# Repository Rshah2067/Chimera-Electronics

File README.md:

# Chimera-Electronics
Chimera is a beetleweight combat robot being designed to compete at NHRL. It has a flamethrower as a main weapon and 2 lifting forks to high center and burn the underside of opponents. This project has the Kicad designs for the custom PCB that controls the robot.

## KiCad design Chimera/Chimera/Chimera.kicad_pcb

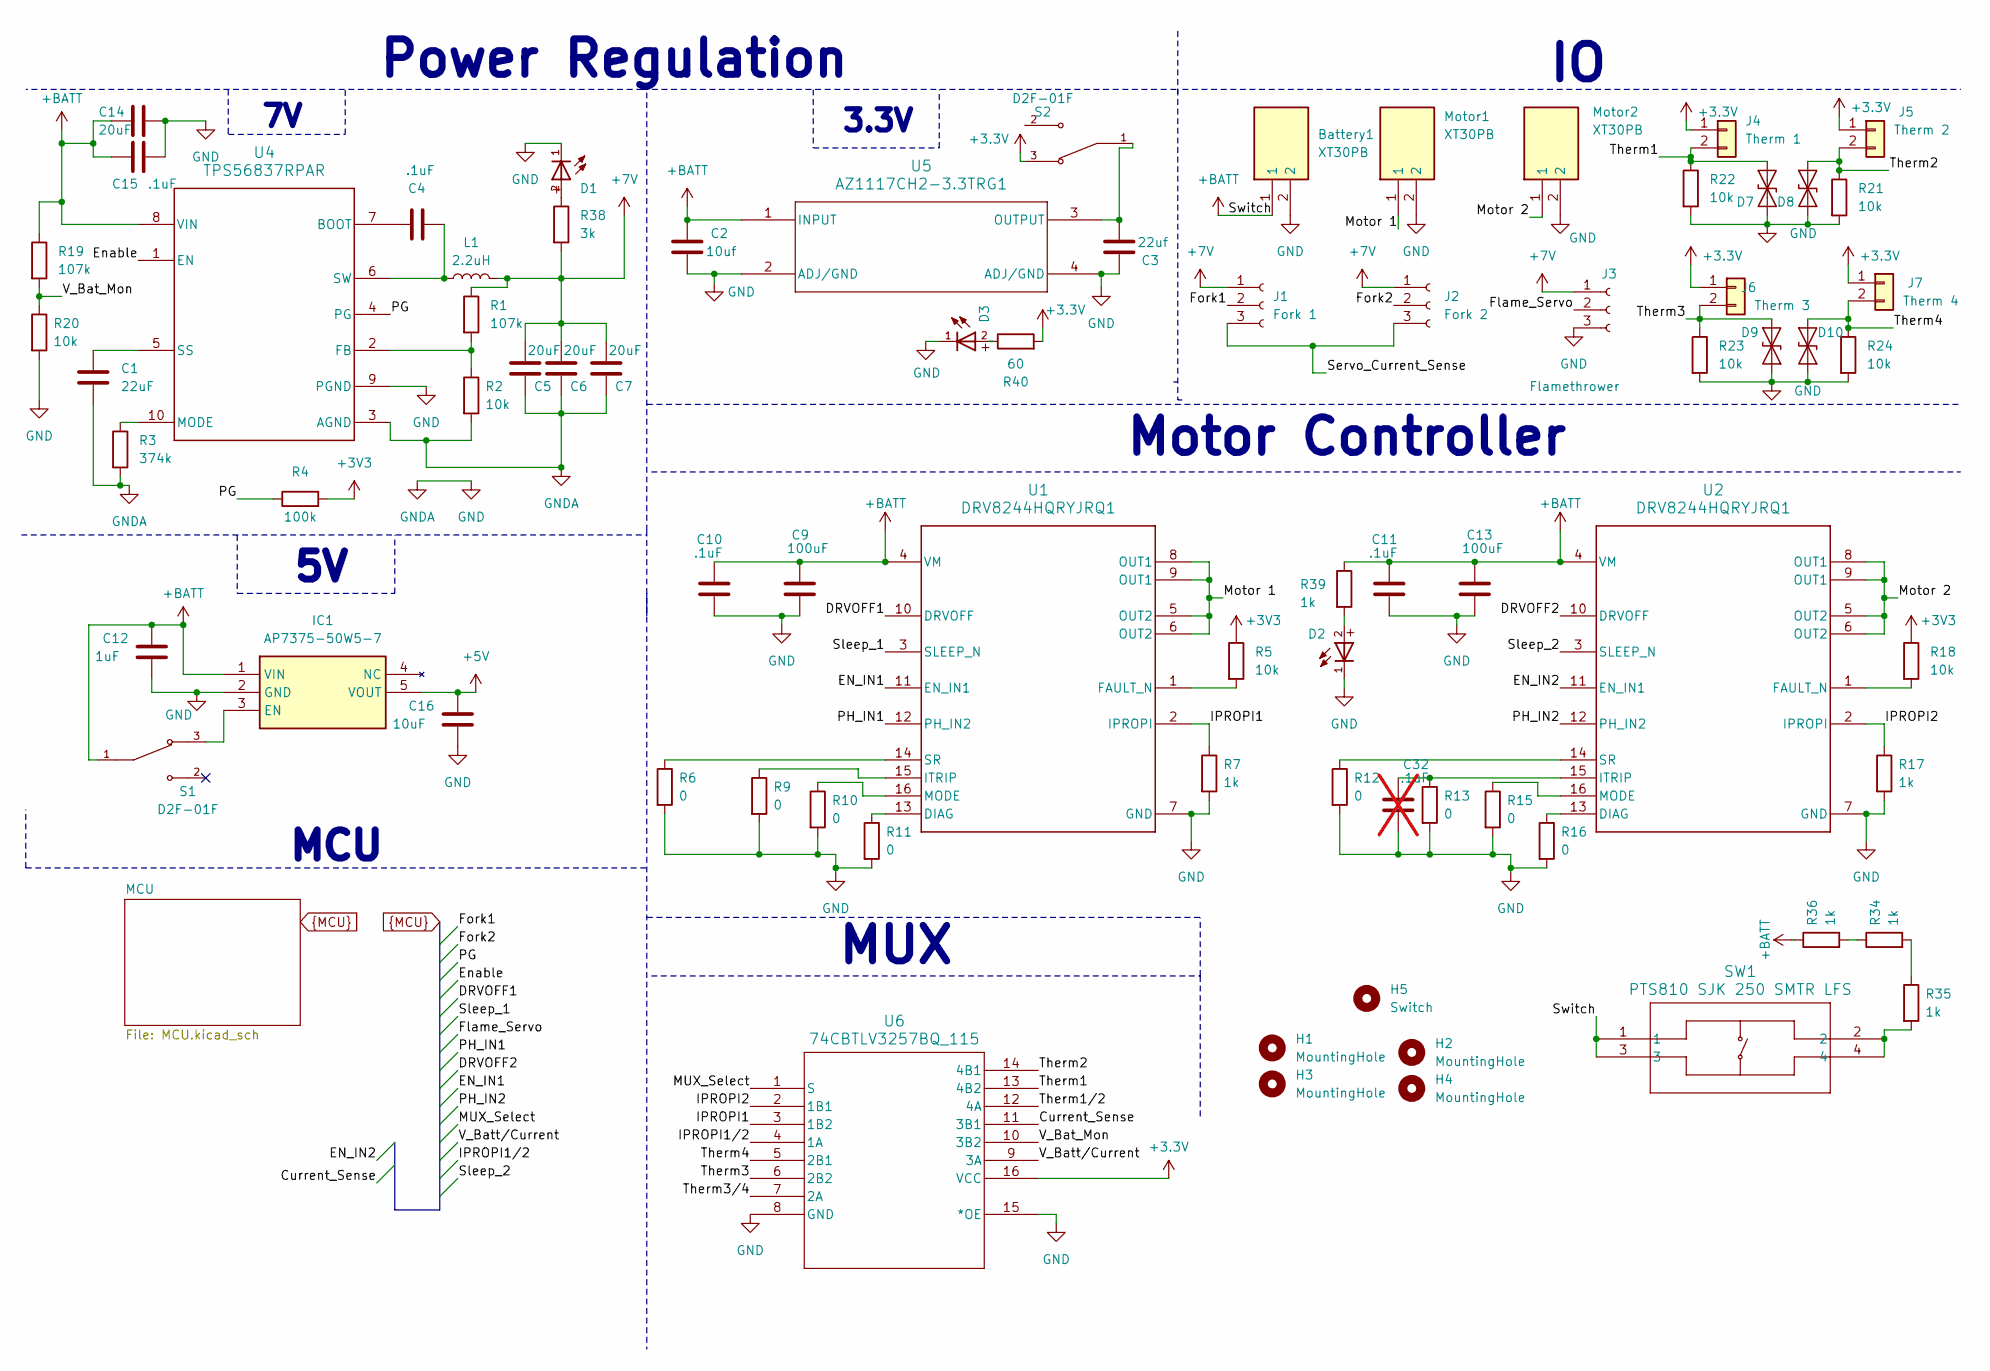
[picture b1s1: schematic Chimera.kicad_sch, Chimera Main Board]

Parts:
Battery1: XT30PB; Manufacturer_Part_Number XT30PB
C1: 22uF; C_0805_2012Metric
C2: 10uf; C_0805_2012Metric
C3: 22uf; C_0805_2012Metric
C4, C10, C11, C15: .1uF; C_0805_2012Metric
C5, C6, C7, C14: 20uF; CAPC1810X80N
C9, C13: 100uF; PCAP_6.3x7.7-ELECT_NCA-M
C12: 1uF; C_0805_2012Metric
C16: 10uF; C_0805_2012Metric
C32: .1uF; C_0805_2012Metric; not fitted
D1, D2, D3: WL-SMCD_0603
D7, D8, D9, D10: SMAJ8.0CA; D_0603_1608Metric
H1, H2, H3, H4: MountingHole; MountingHole_3.2mm_M3
H5: Switch; MountingHole_3.2mm_M3
IC1: AP7375-50W5-7; SOT95P285X140-5N; Manufacturer_Part_Number AP7375-50W5-7; Mouser Part Number 621-AP7375-50W5-7
J1: Fork 1; PinSocket_1x03_P2.54mm_Vertical
J2: Fork 2; PinSocket_1x03_P2.54mm_Vertical
J3: Flamethrower; PinSocket_1x03_P2.54mm_Vertical
J4: Therm 1; PinSocket_1x02_P2.54mm_Vertical
J5: Therm 2; PinSocket_1x02_P2.54mm_Vertical
J6: Therm 3; PinSocket_1x02_P2.54mm_Vertical
J7: Therm 4; PinSocket_1x02_P2.54mm_Vertical
L1: 2.2uH; IND_IHLP-3232DZ_VIS-L
Motor1, Motor2: XT30PB; Manufacturer_Part_Number XT30PB
R1, R19: 107k; R_0805_2012Metric
R2, R5, R18, R20, R21, R22, R23, R24: 10k; R_0805_2012Metric
R3: 374k; R_0805_2012Metric
R4: 100k; R_0805_2012Metric
R6, R9, R10, R11, R12, R13, R15, R16: 0; R_0805_2012Metric
R7, R17, R34, R35, R36, R39: 1k; R_0805_2012Metric
R38: 3k; R_0805_2012Metric
R40: 60; R_0805_2012Metric
S1, S2: D2F-01F; SW_D2F-01F; PARTREV B036-E1-12
SW1: PTS810 SJK 250 SMTR LFS; PTS810_CNK
U1, U2: DRV8244HQRYJRQ1; RYJ0016A-MFG
U4: TPS56837RPAR; CONV_TPS56837RPAR
U5: AZ1117CH2-3.3TRG1; SOT223_DIO-M
U6: 74CBTLV3257BQ_115; IC_74HC138PW-Q100_118

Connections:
+5V: C16.2, IC1.5 (VOUT); also elsewhere on the board
+7.5V: C5.2, C6.2, C7.2, J1.1, J2.1, J3.1, L1.2, R1.1, R38.2
+BATT: Battery1.1, C2.1, C9.1, C10.2, C11.2, C12.2, C13.1, C14.2, C15.2, IC1.1 (VIN), R19.1, R36.1, R39.1, S1.1, SW1.1, SW1.3, U1.4 (VM), U2.4 (VM), U4.8 (VIN), U5.1 (INPUT); also elsewhere on the board
/IPROPI1: R7.1, U1.2 (IPROPI), U6.3 (1B2)
/Motor 1: Motor1.1, U1.5 (OUT2), U1.6 (OUT2), U1.8 (OUT1), U1.9 (OUT1)
/Motor 2: Motor2.1, U2.5 (OUT2), U2.6 (OUT2), U2.8 (OUT1), U2.9 (OUT1); also elsewhere on the board
/Therm1: D7.2 (A2), J4.2, R22.1, U6.13 (4B2); also elsewhere on the board
/Therm2: D8.2 (A2), J5.2, R21.1, U6.14 (4B1); also elsewhere on the board
/Therm3: D9.2 (A2), J6.2, R23.1, U6.6 (2B2); also elsewhere on the board
/Therm4: D10.2 (A2), J7.2, R24.1, U6.5 (2B1); also elsewhere on the board
/V_Bat_Mon: R19.2, R20.1, U6.10 (3B2)
Current_Sense: U6.11 (3B1); also elsewhere on the board
DRVOFF1: U1.10 (DRVOFF); also elsewhere on the board
EN_IN1: U1.11 (EN_IN1); also elsewhere on the board
Enable: U4.1 (EN); also elsewhere on the board
Flame_Servo: J3.2; also elsewhere on the board
Fork1: J1.2; also elsewhere on the board
Fork2: J2.2; also elsewhere on the board
GND: Battery1.2, C1.2, C2.2, C3.1, C5.1, C6.1, C7.1, C9.2, C10.1, C11.1, C12.1, C13.2, C14.1, C15.1, C16.1, C32.1, D1.1, D2.1, D3.1, D7.1 (A1), D8.1 (A1), D9.1 (A1), D10.1 (A1), IC1.2 (GND), J3.3, Motor1.2, Motor2.2, R2.2, R3.2, R6.2, R7.2, R9.2, R10.2, R11.2, R12.2, R13.2, R15.2, R16.2, R17.2, R20.2, R21.2, R22.2, R23.2, R24.2, U1.7 (GND), U2.7 (GND), U4.3 (AGND), U4.9 (PGND), U5.2 (ADJ/GND), U5.4 (ADJ/GND), U6.8 (GND), U6.15 (*OE); also elsewhere on the board
IPROPI1/2: U6.4 (1A); also elsewhere on the board
IPROPI2: R17.1, U2.2 (IPROPI), U6.2 (1B1); also elsewhere on the board
MUX_Select: U6.1 (S); also elsewhere on the board
unnamed: D1.2, R38.1
unnamed: D2.2, R39.2
unnamed: D3.2, R40.1
unnamed 49: IC1.3 (EN), S1.3; also elsewhere on the board
unnamed: R34.1, R36.2
unnamed: R34.2, R35.1
unnamed: R35.2, SW1.2, SW1.4
unnamed: R11.1, U1.13 (DIAG)
unnamed: R5.2, U1.1 (FAULT_N)
unnamed: R9.1, U1.15 (ITRIP)
unnamed: R10.1, U1.16 (MODE)
unnamed: R6.1, U1.14 (SR)
unnamed 59: R16.1, U2.13 (DIAG); also elsewhere on the board
unnamed 60: R18.2, U2.1 (FAULT_N); also elsewhere on the board
unnamed 61: C32.2, R13.1, U2.15 (ITRIP); also elsewhere on the board
unnamed 62: R15.1, U2.16 (MODE); also elsewhere on the board
unnamed 63: R12.1, U2.14 (SR); also elsewhere on the board
unnamed: C4.1, U4.7 (BOOT)
unnamed: R1.2, R2.1, U4.2 (FB)
unnamed: R3.1, U4.10 (MODE)
unnamed: C1.1, U4.5 (SS)
unnamed: C4.2, L1.1, U4.6 (SW)
unnamed 74: C3.2, S2.1, U5.3 (OUTPUT); also elsewhere on the board
PG: R4.1, U4.4 (PG); also elsewhere on the board
PH_IN1: U1.12 (PH_IN2); also elsewhere on the board
Servo_Current_Sense: J1.3, J2.3; also elsewhere on the board
Sleep_1: U1.3 (SLEEP_N); also elsewhere on the board
Therm1/2: U6.12 (4A); also elsewhere on the board
Therm3/4: U6.7 (2A); also elsewhere on the board
V_Batt/Current: U6.9 (3A); also elsewhere on the board

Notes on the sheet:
MCU
Power Regulation
MUX
3.3V
Motor Controller

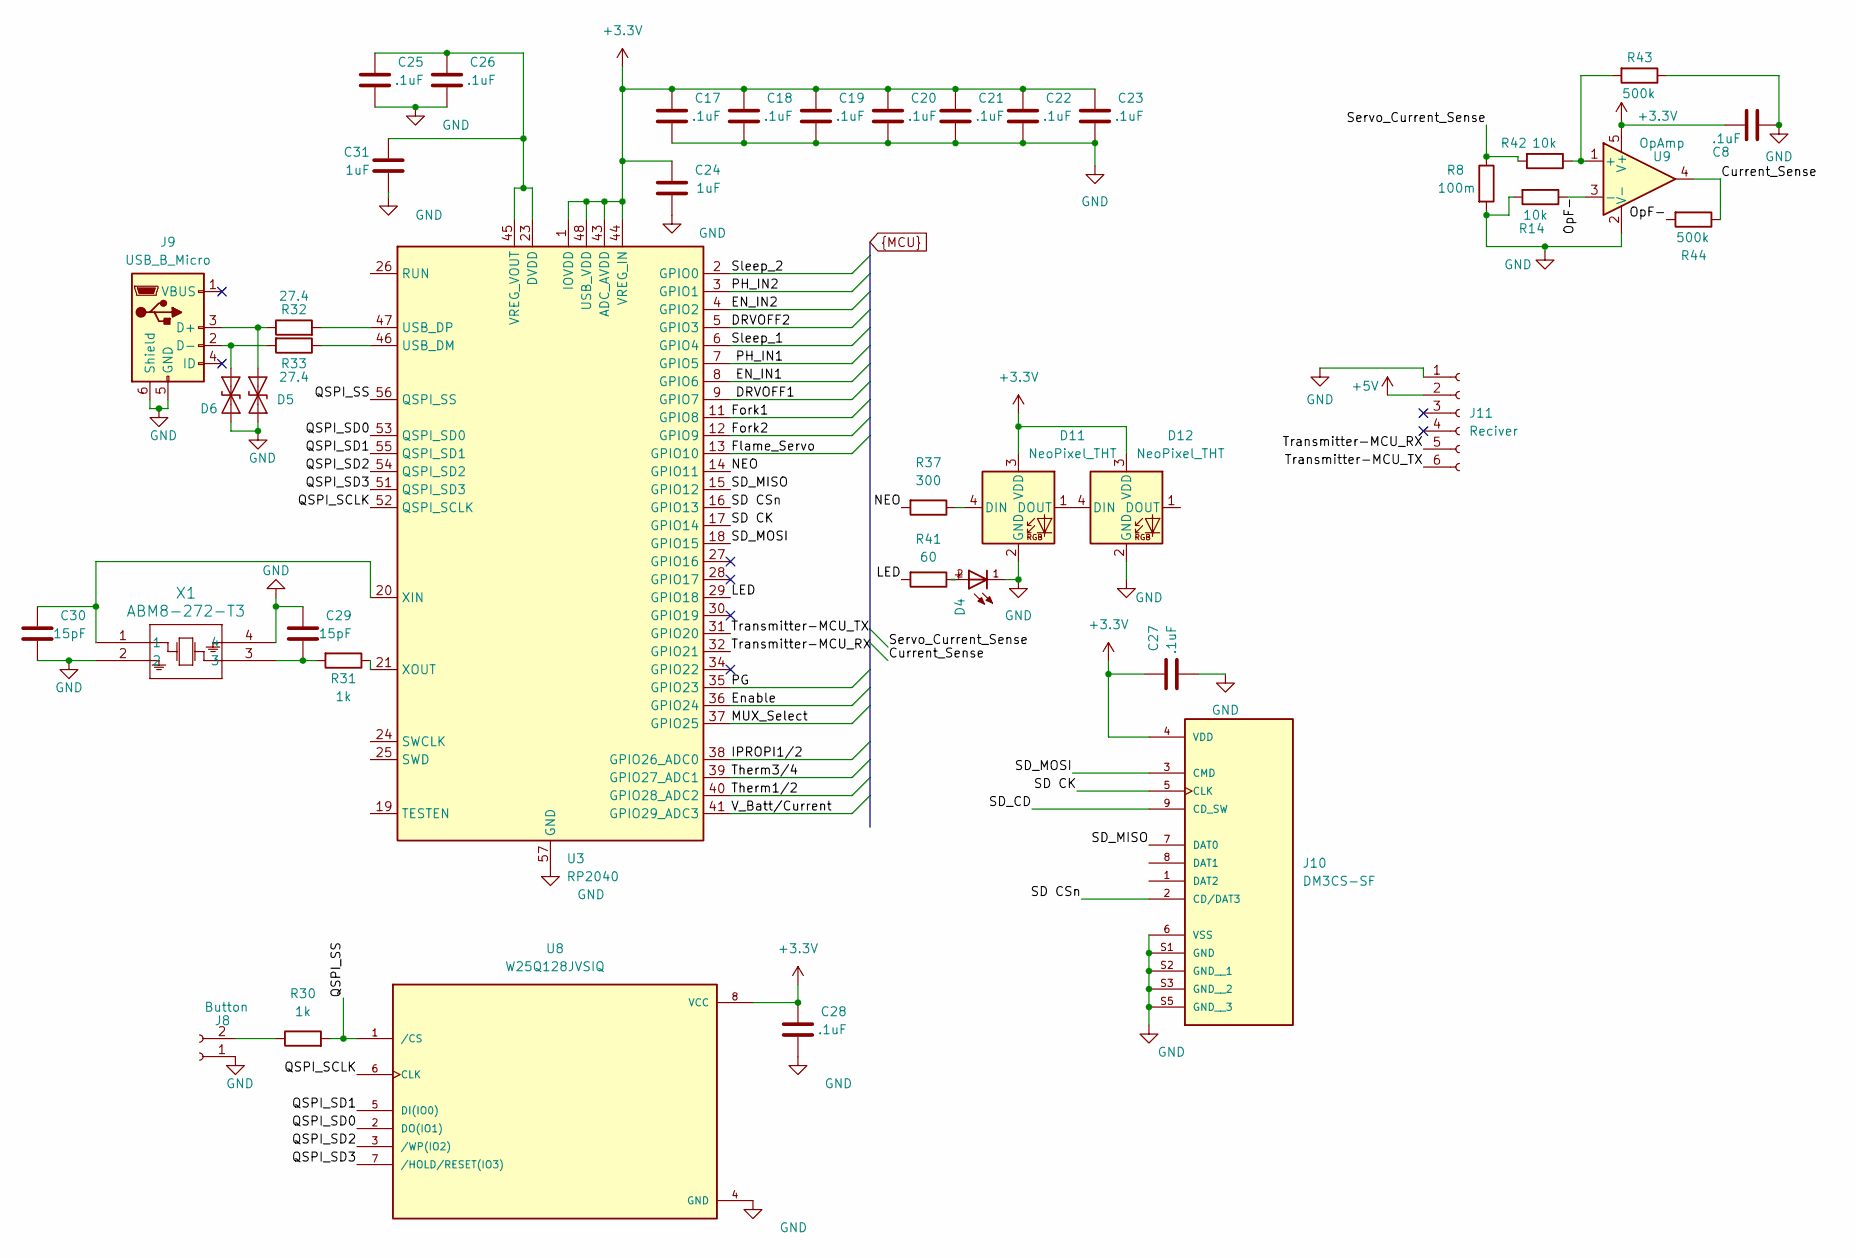
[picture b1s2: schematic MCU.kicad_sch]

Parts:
C8, C17, C18, C19, C20, C21, C22, C23, C25, C26, C27, C28: .1uF; C_0805_2012Metric
C24, C31: 1uF; C_0805_2012Metric
C29, C30: 15pF; C_0805_2012Metric
D4: WL-SMCD_0603
D5, D6: SMAJ8.0CA; D_0603_1608Metric
D11, D12: NeoPixel_THT; WS2812B
J8: Button; PinSocket_1x02_P2.54mm_Vertical
J9: USB_B_Micro; USB_Micro-B_Amphenol_10118194_Horizontal
J10: DM3CS-SF; HRS_DM3CS-SF; PARTREV n/a
J11: Reciver; JST_SH_SM06B-SRSS-TB_1x06-1MP_P1.00mm_Horizontal
R8: 100m; R_0805_2012Metric
R14, R42: 10k; R_0805_2012Metric
R30, R31: 1k; R_0805_2012Metric
R32, R33: 27.4; R_0805_2012Metric
R37: 300; R_0805_2012Metric_Pad1.20x1.40mm_HandSolder
R41: 60; R_0805_2012Metric
R43, R44: 500k; R_0805_2012Metric
U3: RP2040; QFN-56-1EP_7x7mm_P0.4mm_EP3.2x3.2mm
U8: W25Q128JVSIQ; SOIC127P790X216-8N; PARTREV I
U9: OpAmp; SC70-5_LT_MCH-M
X1: ABM8-272-T3; ABM8-272-T3_ABR

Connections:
+5V: J11.2; also elsewhere on the board
/MCU/LED: R41.2, U3.29 (GPIO18)
/MCU/NEO: R37.2, U3.14 (GPIO11)
/MCU/OpF-: R14.1, R44.2, U9.3 (-)
/MCU/QSPI_SCLK: U3.52 (QSPI_SCLK), U8.6 (CLK)
/MCU/QSPI_SD0: U3.53 (QSPI_SD0), U8.2 (DO(IO1))
/MCU/QSPI_SD1: U3.55 (QSPI_SD1), U8.5 (DI(IO0))
/MCU/QSPI_SD2: U3.54 (QSPI_SD2), U8.3 (/WP(IO2))
/MCU/QSPI_SD3: U3.51 (QSPI_SD3), U8.7 (/HOLD/RESET(IO3))
/MCU/QSPI_SS: R30.2, U3.56 (QSPI_SS), U8.1 (/CS)
/MCU/SD CK: J10.5 (CLK), U3.17 (GPIO14)
/MCU/SD CSn: J10.2 (CD/DAT3), U3.16 (GPIO13)
/MCU/SD_CD: J10.9 (CD_SW)
/MCU/SD_MISO: J10.7 (DAT0), U3.15 (GPIO12)
/MCU/SD_MOSI: J10.3 (CMD), U3.18 (GPIO15)
/MCU/Transmitter-MCU_RX: J11.5, U3.32 (GPIO21)
/MCU/Transmitter-MCU_TX: J11.6, U3.31 (GPIO20)
Current_Sense: R44.1, U9.4; also elsewhere on the board
DRVOFF1: U3.9 (GPIO7); also elsewhere on the board
DRVOFF2: U3.5 (GPIO3); also elsewhere on the board
EN_IN1: U3.8 (GPIO6); also elsewhere on the board
EN_IN2: U3.4 (GPIO2); also elsewhere on the board
Enable: U3.36 (GPIO24); also elsewhere on the board
Flame_Servo: U3.13 (GPIO10); also elsewhere on the board
Fork1: U3.11 (GPIO8); also elsewhere on the board
Fork2: U3.12 (GPIO9); also elsewhere on the board
GND: C8.1, C17.1, C18.1, C19.1, C20.1, C21.1, C22.1, C23.1, C24.1, C25.1, C26.1, C27.1, C28.1, C29.2, C30.1, C31.1, D4.1, D5.1 (A1), D6.1 (A1), D11.2 (GND), D12.2 (GND), J8.1, J9.5 (GND), J9.6 (Shield), J10.6 (VSS), J10.S1 (GND), J10.S2 (GND__1), J10.S3 (GND__2), J10.S5 (GND__3), J11.1, R8.2, R14.2, R43.1, U3.57 (GND), U8.4 (GND), U9.2 (V-), X1.2, X1.4; also elsewhere on the board
IPROPI1/2: U3.38 (GPIO26_ADC0); also elsewhere on the board
MUX_Select: U3.37 (GPIO25); also elsewhere on the board
unnamed: C29.1, R31.2, X1.3
unnamed: D4.2, R41.1
unnamed: D5.2 (A2), J9.3 (D+), R32.1
unnamed: D6.2 (A2), J9.2 (D-), R33.2
unnamed: D11.4 (DIN), R37.1
unnamed: D11.1 (DOUT), D12.4 (DIN)
unnamed: J8.2, R30.1
unnamed: R33.1, U3.46 (USB_DM)
unnamed: R32.2, U3.47 (USB_DP)
unnamed: C25.2, C26.2, C31.2, U3.23 (DVDD), U3.45 (VREG_VOUT), U3.50 (DVDD)
unnamed: C30.2, U3.20 (XIN), X1.1
unnamed: R31.1, U3.21 (XOUT)
unnamed: R42.1, R43.2, U9.1 (+)
PG: U3.35 (GPIO23); also elsewhere on the board
PH_IN1: U3.7 (GPIO5); also elsewhere on the board
PH_IN2: U3.3 (GPIO1); also elsewhere on the board
Servo_Current_Sense: R8.1, R42.2; also elsewhere on the board
Sleep_1: U3.6 (GPIO4); also elsewhere on the board
Sleep_2: U3.2 (GPIO0); also elsewhere on the board
Therm1/2: U3.40 (GPIO28_ADC2); also elsewhere on the board
Therm3/4: U3.39 (GPIO27_ADC1); also elsewhere on the board
V_Batt/Current: U3.41 (GPIO29_ADC3); also elsewhere on the board

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
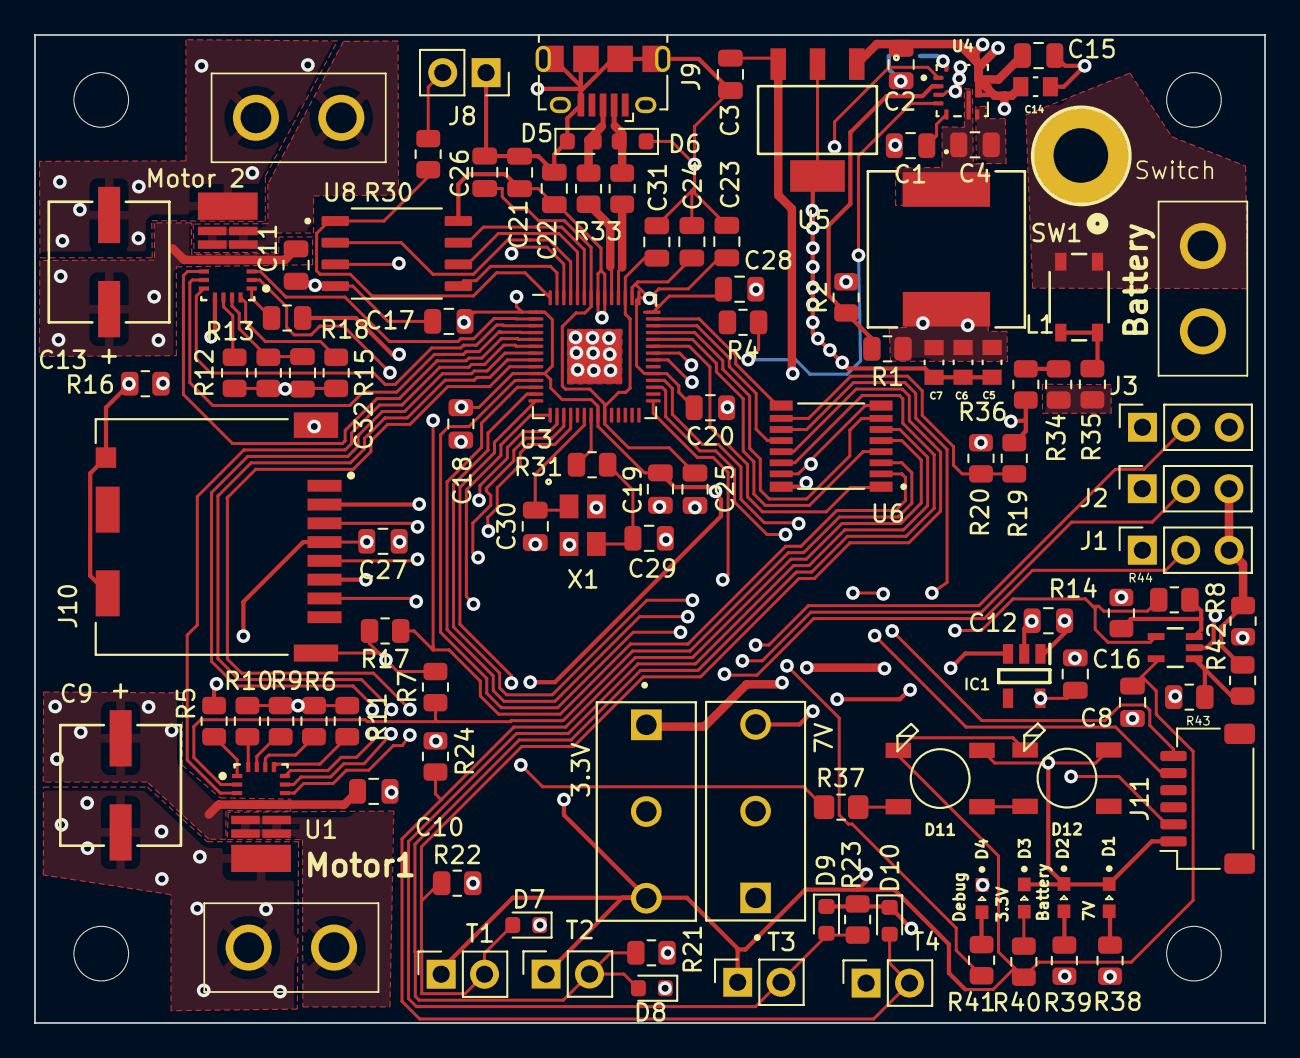
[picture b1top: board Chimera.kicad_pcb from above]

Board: 4 copper layers, 72.0 x 57.9 mm, 116 parts (1 on the bottom side), 85 nets.

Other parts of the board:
3.3V, 7V: D2F-01F; SW_D2F-01F
Battery: XT30PB
H6: MountingHole; MountingHole_3.2mm_M3
Motor 2: DRV8244HQRYJRQ1; RYJ0016A-MFG
Switch: Switch; screwswitch
T1: Therm 1; PinSocket_1x02_P2.54mm_Vertical
T2: Therm 2; PinSocket_1x02_P2.54mm_Vertical
T3: Therm 3; PinSocket_1x02_P2.54mm_Vertical
T4: Therm 4; PinSocket_1x02_P2.54mm_Vertical

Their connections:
+BATT: 7V.1, Battery.1, Motor 2.4 (VM), Switch.0 (in); also elsewhere on the board
/Motor 2: Motor 2.5 (OUT2), Motor 2.6 (OUT2), Motor 2.8 (OUT1), Motor 2.9 (OUT1); also elsewhere on the board
/Therm1: T1.2; also elsewhere on the board
/Therm2: T2.2; also elsewhere on the board
/Therm3: T3.2; also elsewhere on the board
/Therm4: T4.2; also elsewhere on the board
DRVOFF2: Motor 2.10 (DRVOFF); also elsewhere on the board
EN_IN2: Motor 2.11 (EN_IN1); also elsewhere on the board
GND: Battery.2, Motor 2.7 (GND); also elsewhere on the board
IPROPI2: Motor 2.2 (IPROPI); also elsewhere on the board
unnamed 49: 7V.3; also elsewhere on the board
unnamed 59: Motor 2.13 (DIAG); also elsewhere on the board
unnamed 60: Motor 2.1 (FAULT_N); also elsewhere on the board
unnamed 61: Motor 2.15 (ITRIP); also elsewhere on the board
unnamed 62: Motor 2.16 (MODE); also elsewhere on the board
unnamed 63: Motor 2.14 (SR); also elsewhere on the board
unnamed 74: 3.3V.1; also elsewhere on the board
PH_IN2: Motor 2.12 (PH_IN2); also elsewhere on the board
Sleep_2: Motor 2.3 (SLEEP_N); also elsewhere on the board

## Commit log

2024-09-16 switching to main branch
2024-09-20 retrive
2024-09-20 Restored Deleted Files
2024-09-24 Rewiring M2 and moved Debugging LEDS
2024-10-05 added reciever and fixed wiring below MCU
2024-10-25 Saving changes, to revert and look at previous routing
2024-10-25 Fixed roughting on MUX, some minor details left for thermistor traces
2024-11-12 Finalized MUX and thermistor wiring, Need to revise Buck and add Opamp surronding circuitry
2024-11-28 Final Board and BOM
2024-11-28 Added board STEP File
2024-11-28 Added Board CAD
